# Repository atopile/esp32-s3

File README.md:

## Overview
[atopile](https://atopile.io/) is a tool to build electronic circuit boards with code. It brings the best of software development to the world of hardware design.

The atopile [package registry](https://packages.atopile.io/) contains a list of existing ato packages. Packages usually contain components, module footprints, and layouts that can be reused in other projects.

A package usually points to a git repository (such as this one) that contains the design files, in a similar fashion to a standard atopile project.

The ESP32-S3 is a powerful, versatile microcontroller designed for IoT applications. It features dual-core Xtensa LX7 processors, Wi-Fi and Bluetooth 5 connectivity, rich I/O capabilities, and enhanced security features, making it ideal for smart home devices, wearable electronics, and automated systems requiring efficient processing and wireless communication.

## Features
Power interface: 3.3V input
SPI interface: 4-wire SPI
I2C interface
JTAG interface

## Contributing
Contribute to this package using pull requests.

## License
This battery connector module is provided under the MIT License.

## Contact
For further inquiries or support, please contact me at narayan@atopile.io.

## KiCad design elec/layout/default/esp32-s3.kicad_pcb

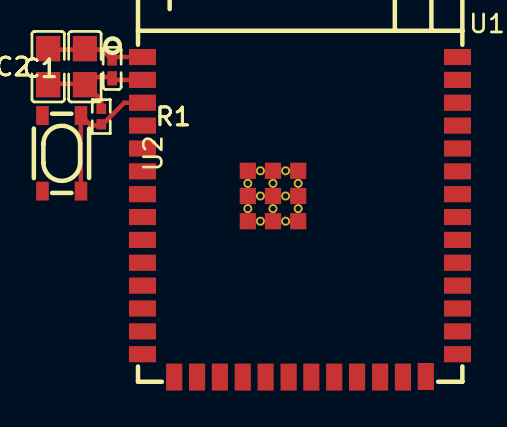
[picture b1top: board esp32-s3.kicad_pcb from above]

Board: 2 copper layers, 6 parts (0 on the bottom side), 3 nets.

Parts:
C1: 100nF ±10% 16V X7R; C0402-b3ef17
C2, C3: 10µF ±10% 25V X5R; C0805-3b2e55
R1: 10kΩ ±1% 62.5mW; R0402-56259e
U1: WIRELM-SMD_ESP32-S3-WROOM-1
U2: KEY-SMD_4P-L4.2-W3.2-P2.20-LS4.6

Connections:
en: R1.2, U1.3, U2.1, U2.2
ic-gnd: C1.2, C2.2, C3.2, U1.1, U1.40, U1.41, U2.3, U2.4
vcc: C1.1, C2.1, C3.1, R1.1, U1.2

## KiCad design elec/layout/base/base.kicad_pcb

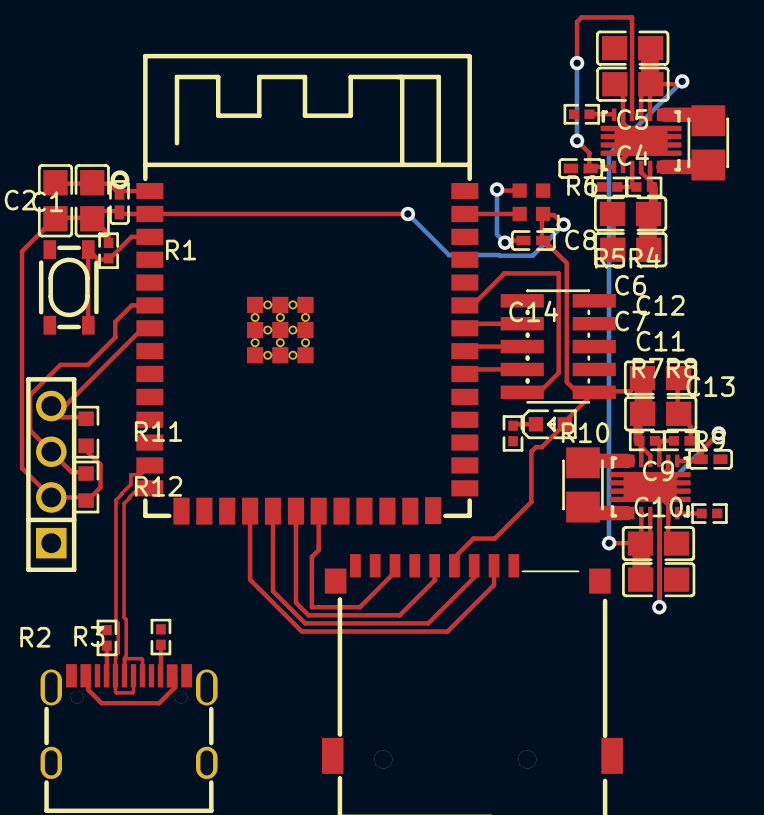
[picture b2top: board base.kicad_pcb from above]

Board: 2 copper layers, 38 parts (0 on the bottom side), 32 nets.

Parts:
C1, C8, C13, C14: 100nF ±10% 16V X7R; C0402-b3ef17
C2, C3, C4, C5, C6, C7, C9, C10, C11, C12: 10µF ±10% 25V X5R; C0805-3b2e55
L1, L2: 1.5µH ±20%; IND-SMD_L2.5-W2.0_WPN252012H
LED1: 2V; LED0603-RD
R1: 10kΩ ±1% 62.5mW; R0402-56259e
R2, R3: 4.7kΩ ±1% 62.5mW; R0402-56259e
R4, R7: infΩ infW; R0402-56259e
R5, R8, R10: 1kΩ ±1% 62.5mW; R0402-56259e
R6, R9: 1MΩ ±1% 62.5mW; R0402-56259e
R11, R12: 2.7kΩ ±1% 100mW; R0603-ebcab9
U1: WIRELM-SMD_ESP32-S3-WROOM-1
U2: KEY-SMD_4P-L4.2-W3.2-P2.20-LS4.6
U3: HDR-SMD_10P-P1.27-V-M-R2-C5-LS5.3
U4: USB-C-SMD_KH-TYPE-C-16P
U5, U6: VSON-14_L4.0-W3.0-P0.50-BL-EP_TI_DSJ
U7: TF-SMD_TF-01A
U8: LED-SMD_4P-L2.0-W2.0-BR
U9: HDR-TH_4P-P2.54-V-F

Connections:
_3v3_reg.feedback_div-out: R7.2, R8.1, U6.3
_3v3_reg.ic-l1: L2.1, U6.8, U6.9
_3v3_reg.ic-l2: L2.2, U6.6, U6.7
_3v3_reg.ic-pg: R9.1, U6.14
_3v3_reg.ic-vina: C13.1, U6.1, U6.12
_5v_reg-vcc: C6.1, C7.1, R4.1, U5.4, U5.5
_5v_reg.feedback_div-out: R4.2, R5.1, U5.3
_5v_reg.ic-l1: L1.1, U5.8, U5.9
_5v_reg.ic-l2: L1.2, U5.6, U5.7
_5v_reg.ic-pg: R6.1, U5.14
_5v_reg.ic-vina: C8.1, U5.1, U5.12
cathode: LED1.1, R10.1
cc1: R2.1, U4.A5
cc2: R3.1, U4.B5
cs: U1.18, U7.2
en: R1.2, U1.3, U2.1, U2.2
io1: U1.39, U8.4
miso: U1.21, U7.7
mosi: U1.19, U7.3
sck: U1.20, U7.5
scl: R12.1, U1.6, U9.3
sda: R11.1, U1.7, U9.4
tck: U1.32, U3.4
tdi: U1.34, U3.8
tdo: U1.33, U3.6
tms: U1.35, U3.2
uc.ic-gnd: C1.2, C2.2, C3.2, C4.2, C5.2, C6.2, C7.2, C8.2, C9.2, C10.2, C11.2, C12.2, C13.2, C14.2, R2.2, R3.2, R5.2, R6.2, R8.2, R9.2, R10.2, U1.1, U1.40, U1.41, U2.3, U2.4, U3.3, U3.5, U3.9, U4.1, U4.2, U4.3, U4.4, U4.A1, U4.A12, U4.B1, U4.B12, U5.2, U5.13, U5.15, U6.2, U6.13, U6.15, U7.6, U7.10, U7.11, U7.12, U7.13, U8.3, U9.1
uc.ic-vcc: C1.1, C2.1, C3.1, C11.1, C12.1, C14.1, LED1.2, R1.1, R7.1, R11.2, R12.2, U1.2, U3.1, U6.4, U6.5, U7.4, U8.1, U9.2
usb+: U1.14, U4.A6, U4.B6
usb-: U1.13, U4.A7, U4.B7
usb_conn-vcc: U4.A4, U4.A9, U4.B4, U4.B9
vcc: C4.1, C5.1, C9.1, C10.1, U5.10, U5.11, U6.10, U6.11

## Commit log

2024-01-26 Configure project
2024-01-26 initial design
2024-01-31 updating readme and adding SPI and I2C interfaces
2024-02-03 changing case of module name
2024-02-03 fix entry name in ato yaml
2024-02-13 added layout
2024-02-14 changed usb interface name to usb2
2024-03-07 updated pin passthrough
2024-03-08 layout updates
2024-07-05 Remove xmas tree from layout
2024-10-15 Add bear necessities 🧸
2024-10-15 Add layout for base
2024-10-15 Add connector for display
2024-10-15 Add io47 and io48 to shims in kit
2024-10-16 Add pre-reqs for power-prioritiser
2024-10-16 Add pulls to i2c lines
2024-10-16 Add i2c pullups
2024-10-18 Fix and sync layout
2024-10-18 Add footprint for power-prioritiser FET
2024-10-18 Add PFET footprint
2024-10-18 Fix footprints in base module
2024-10-28 Move power-prioritiser to it's own repo
2024-12-18 Use linked, updated generics
2025-01-16 run build with 0.3 compiler
2025-01-16 Revert "run build with 0.3 compiler"
2025-01-18 Update to build with the v0.3 compiler
2025-02-04 Fix and relink layouts. Apply v0.3 updates
2025-02-05 Remove stray net
2025-03-07 Remove base build, relink layout
2025-03-07 Update ci.yml
    update actions
    use main
2025-04-05 update to kicad 9 and update JTAG interface
2025-04-05 build with latest
